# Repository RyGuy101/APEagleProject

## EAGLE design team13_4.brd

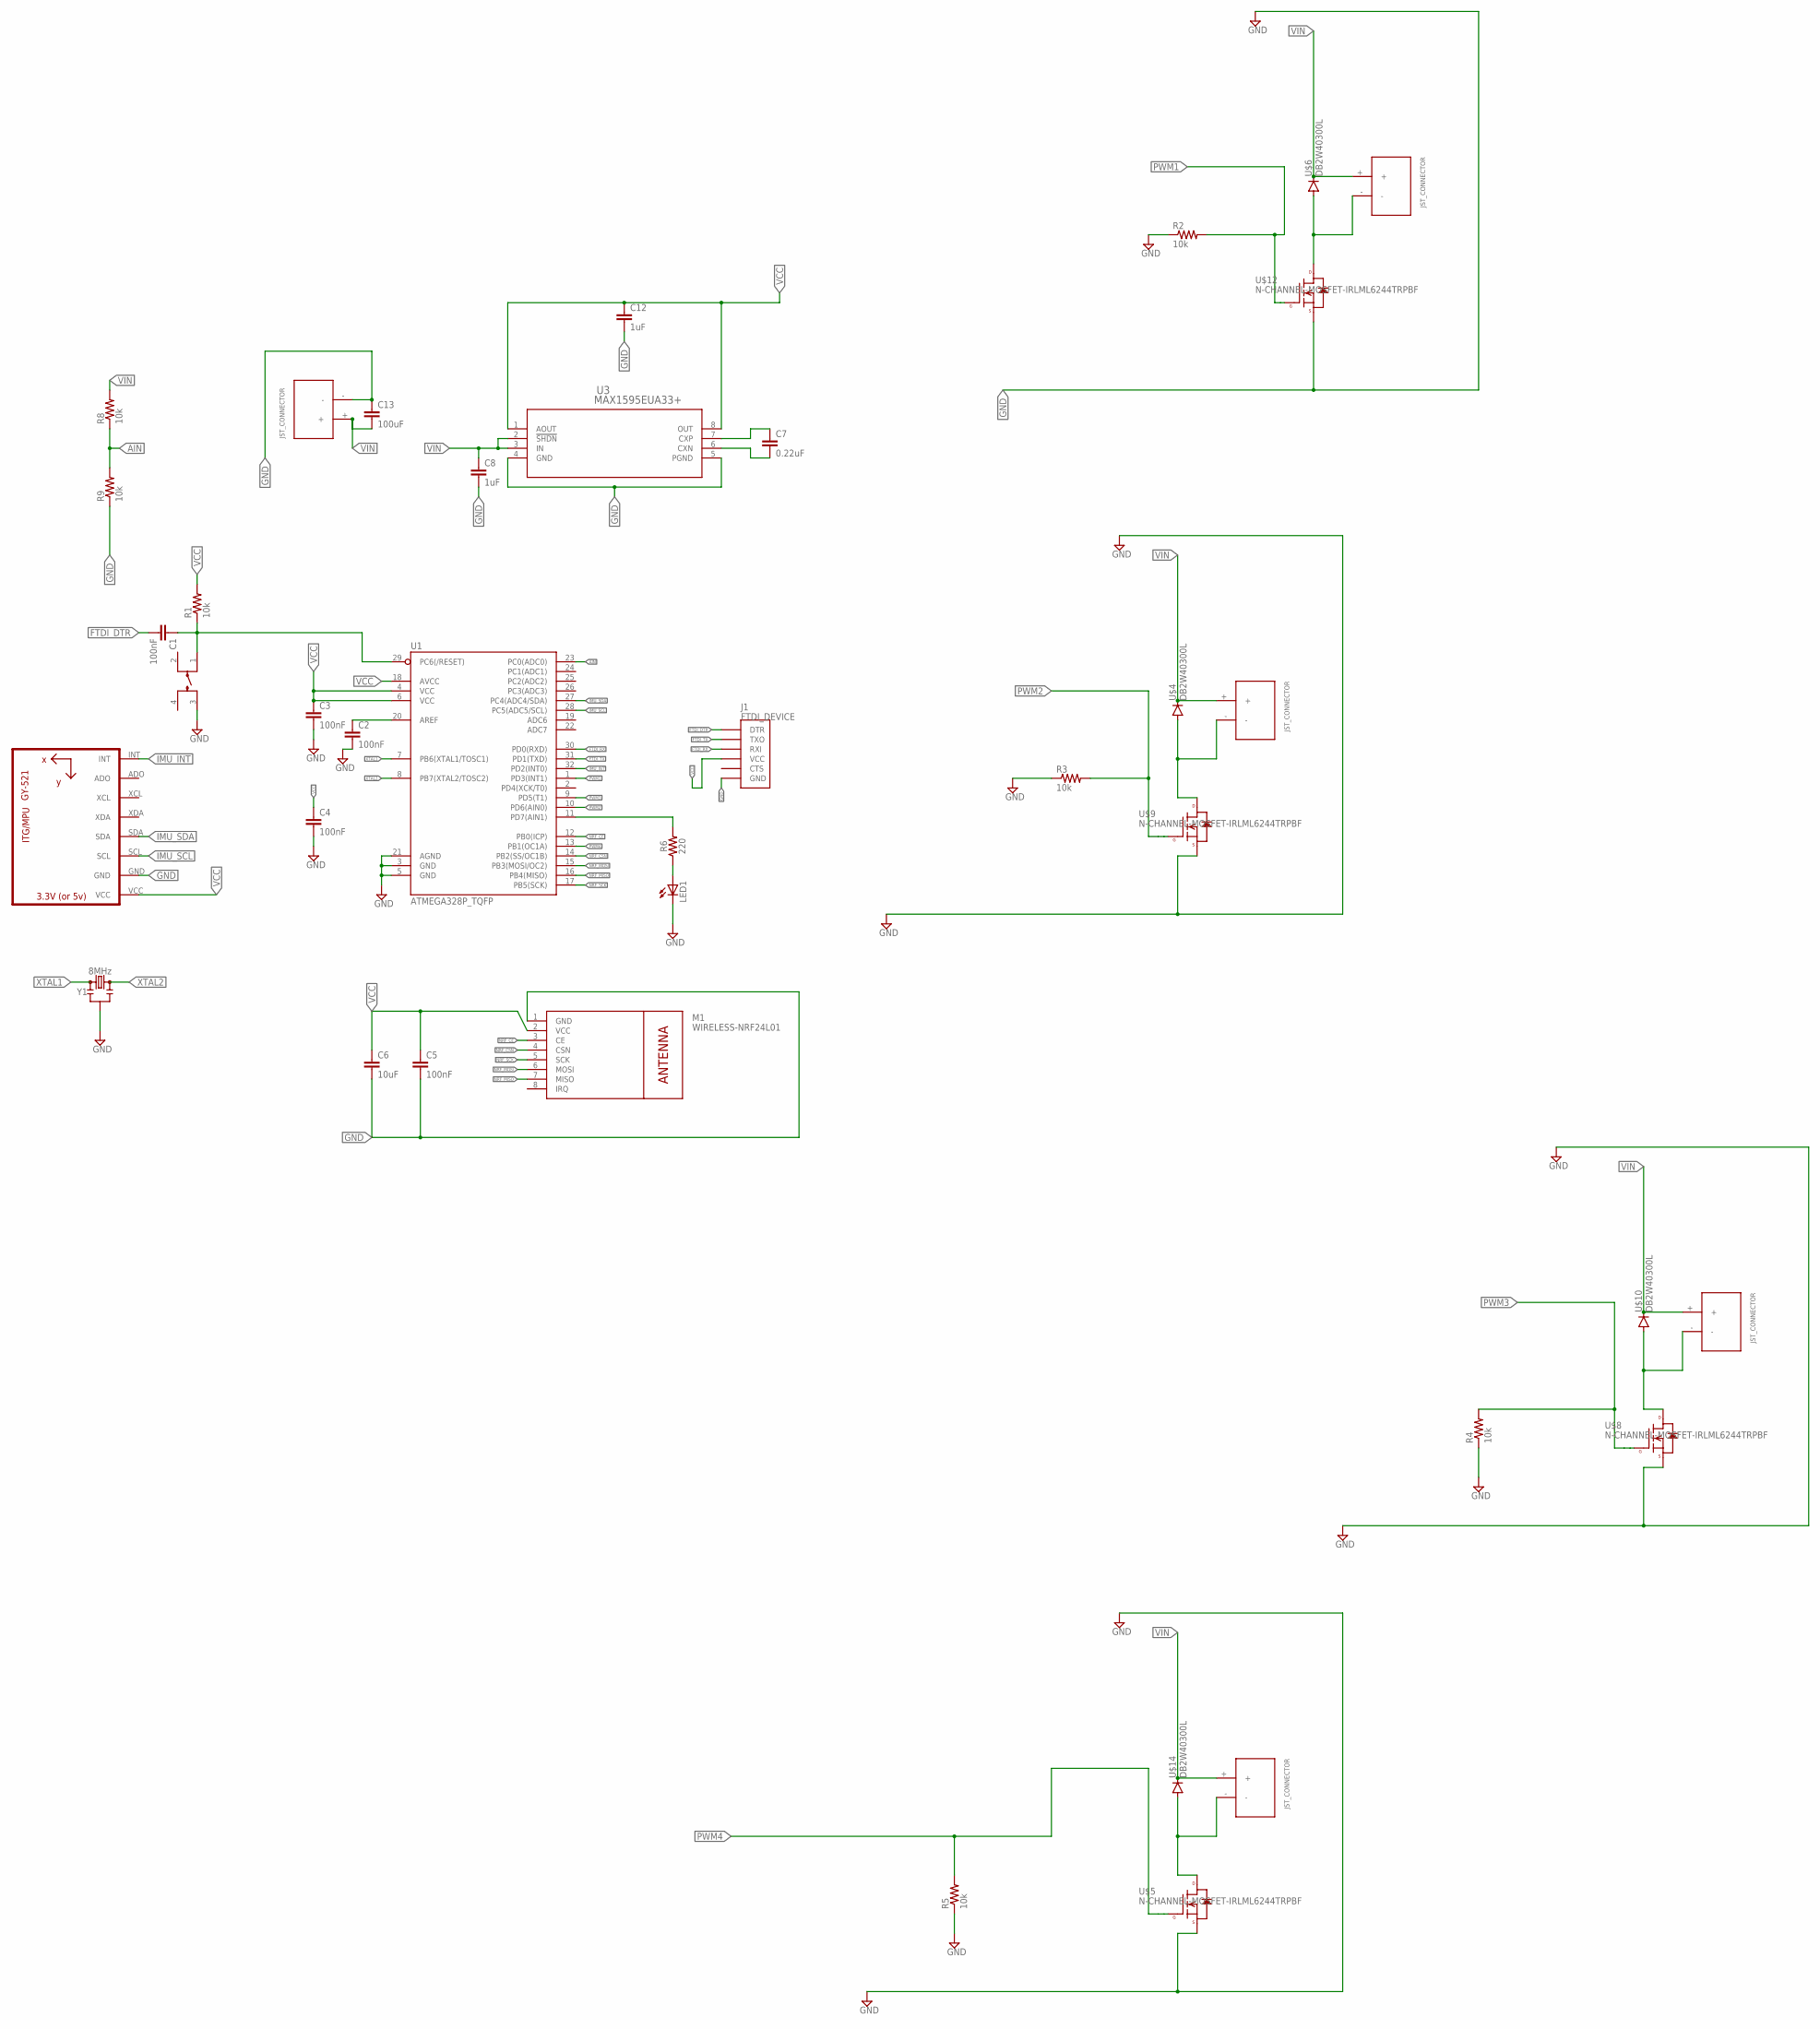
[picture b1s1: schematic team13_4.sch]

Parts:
C1, C2, C3, C4, C5: 100nF; C0603
C6: 10uF; C0603
C7: 0.22uF; C0603
C8, C12: 1uF; C0805
C13: 100uF; C1210
J1: FTDI_DEVICE; FTDI_DEVICE_SIDE
LED1: LED1206; LED-1206
M1: WIRELESS-NRF24L01
R1, R8, R9: 10k; R0603
R2, R3, R4, R5: 10k; 0603-RES
R6: 220; 0603
U1: ATMEGA328P_TQFP; TQFP32-08
U2: GY-521MPU6050; GY-521
U3: MAX1595EUA33+; 21-0036K
U$1: LL3301NF065QG
U$3, U$7, U$11, U$15, U$19: JST_CONNECTOR_FEMALE
U$4, U$6, U$10, U$14: DB2W40300L; MINI2-F3-B
U$5, U$8, U$9, U$12: N-CHANNEL-MOSFET-IRLML6244TRPBF; SOT23-3
Y1: 8MHz; RESONATOR-SMD-3.2X1.3

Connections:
AIN: R8.1, R9.2, U1.23 (PC0(ADC0))
FTDI_DTR: C1.2, J1.P$1 (DTR)
FTDI_RX: J1.P$3 (RXI), U1.30 (PD0(RXD))
FTDI_TX: J1.P$2 (TXO), U1.31 (PD1(TXD))
GND: C2.2, C3.2, C4.2, C5.2, C6.2, C8.2, C12.2, C13.1, J1.P$6 (GND), LED1.C, M1.1 (GND), R2.1, R3.1, R4.1, R5.1, R9.1, U1.3 (GND), U1.5 (GND), U1.21 (AGND), U2.GND, U3.4 (GND), U3.5 (PGND), U$1.3, U$5.2 (S), U$8.2 (S), U$9.2 (S), U$12.2 (S), U$19.-, Y1.2
IMU_INT: U1.32 (PD2(INT0)), U2.INT
IMU_SCL: U1.28 (PC5(ADC5/SCL)), U2.SCL
IMU_SDA: U1.27 (PC4(ADC4/SDA)), U2.SDA
unnamed: C1.1, R1.1, U1.29 (PC6(/RESET)), U$1.1
unnamed: C2.1, U1.20 (AREF)
unnamed: U$3.-, U$4.POS (PPIN), U$9.3 (D)
unnamed: C7.1, U3.7 (CXP)
unnamed: R6.2, U1.11 (PD7(AIN1))
unnamed: U$6.POS (PPIN), U$7.-, U$12.3 (D)
unnamed: C7.2, U3.6 (CXN)
unnamed: LED1.A, R6.1
unnamed: U$8.3 (D), U$10.POS (PPIN), U$11.-
unnamed: U$5.3 (D), U$14.POS (PPIN), U$15.-
NRF_CE: M1.3 (CE), U1.12 (PB0(ICP))
NRF_CSN: M1.4 (CSN), U1.14 (PB2(SS/OC1B))
NRF_MISO: M1.7 (MISO), U1.16 (PB4(MISO))
NRF_MOSI: M1.6 (MOSI), U1.15 (PB3(MOSI/OC2))
NRF_SCK: M1.5 (SCK), U1.17 (PB5(SCK))
PWM1: R2.2, U1.1 (PD3(INT1)), U$12.1 (G)
PWM2: R3.2, U1.10 (PD6(AIN0)), U$9.1 (G)
PWM3: R4.2, U1.9 (PD5(T1)), U$8.1 (G)
PWM4: R5.2, U1.13 (PB1(OC1A)), U$5.1 (G)
VCC: C3.1, C4.1, C5.1, C6.1, C12.1, J1.P$4 (VCC), M1.2 (VCC), R1.2, U1.4 (VCC), U1.6 (VCC), U1.18 (AVCC), U2.VCC, U3.1 (AOUT), U3.8 (OUT)
VIN: C8.1, C13.2, R8.2, U3.2 (!SHDN), U3.3 (IN), U$3.+, U$4.NEG (GPIN), U$6.NEG (GPIN), U$7.+, U$10.NEG (GPIN), U$11.+, U$14.NEG (GPIN), U$15.+, U$19.+
XTAL1: U1.7 (PB6(XTAL1/TOSC1)), Y1.1
XTAL2: U1.8 (PB7(XTAL2/TOSC2)), Y1.3

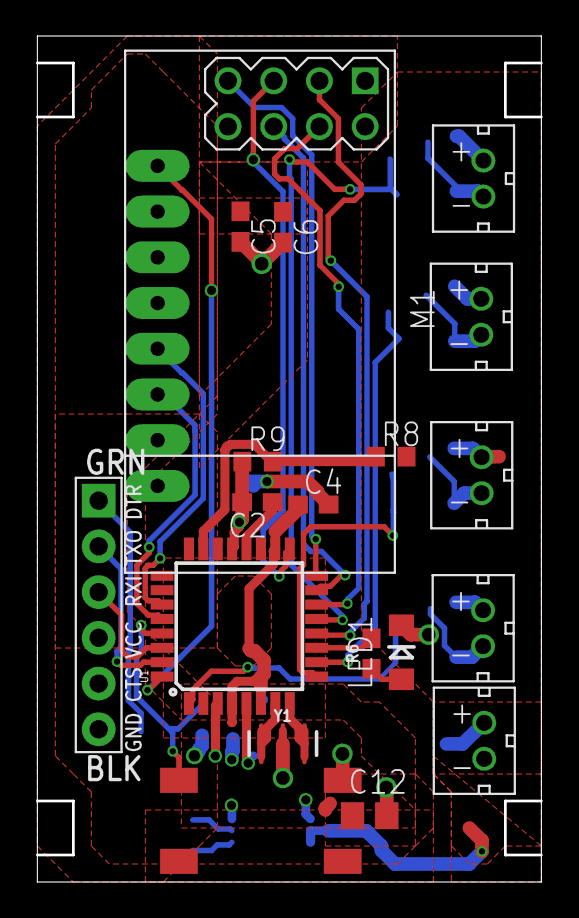
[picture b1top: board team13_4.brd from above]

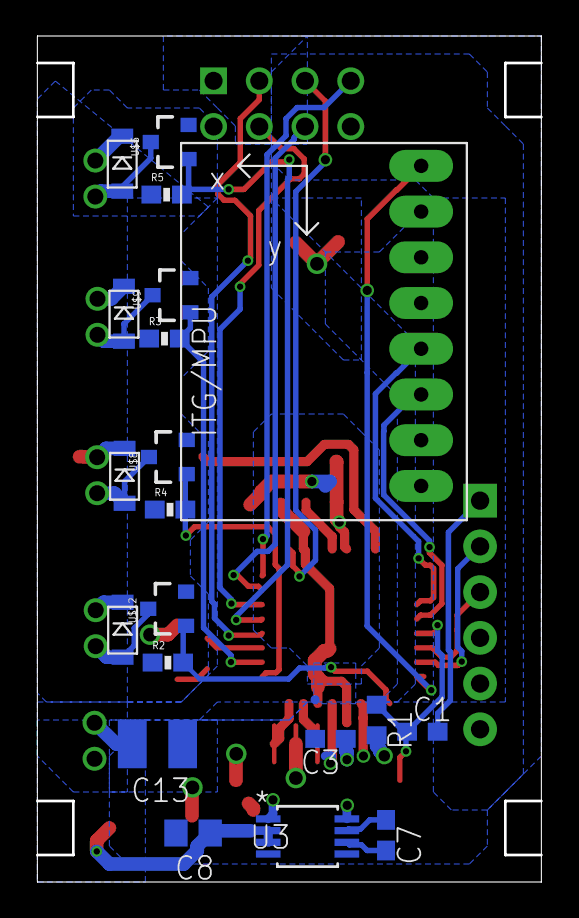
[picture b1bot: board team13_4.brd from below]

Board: 2 copper layers, 28.0 x 46.8 mm, 39 parts (20 on the bottom side), 31 nets.

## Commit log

2018-01-28 Added microcontroller, some decoupling capacitors, headers for FTDI
2018-01-28 Made gitignore
2018-01-29 Added Will's changes
2018-01-29 Added eagle.epf to gitignore
2018-01-29 Added IMU
2018-01-29 Create low side driver
2018-01-29 Updated connections to radio module
2018-01-30 Added buck-boost converter
2018-01-30 Added JST connector
2018-01-30 Added separate radio & buck boost sch
2018-01-30 Added ftdi & decoupling capacitor sch
2018-01-30 added gyro & voltage divider sch
2018-01-30 Added decoupling capacitors to radio module
2018-01-31 Updated schematic. TODO: voltage divider, voltage regulator, motor driver, battery
2018-02-01 Add files via upload
    Lots of stuff
2018-02-01 Updated PWM pins
2018-02-01 Added circuit for crystal oscillator
2018-02-02 Fixed stuff. Replaced crystal & voltage regulator.
2018-02-02 Fixed RX and TX connections
2018-02-02 Made push button library
2018-02-02 Fixed capacitor value
2018-02-02 Fixed some stuff
2018-02-04 Updated capacitors for voltage regulator
2018-02-04 Fixed many overlapping pin ERC errors.
2018-02-04 Saved fixed schematic
2018-02-04 Switched from crystal oscillator to ceramic resonator
2018-02-04 Fixed some of the weird angles
2018-02-04 Removed all angled wires
2018-02-04 Fixed ERC warnings about VCC and GND
2018-02-04 Modified LED Resistor value
2018-02-04 Added changes to voltage regulator and cleaned up pushbutton library.
2018-02-04 "Fixed" another warning caused by voltage regulator.
2018-02-08 Started board design. I love Eagle it's so easy to use.... is a sentence never said by anyone ever.
2018-02-08 Fixed button library. Somehow I had made the pads 2x too big.
2018-02-08 Found the setting for 45 degree routing
2018-02-09 Everything is connected except VCC and GND. But it's really messy and it might even be impossible to connect them successfully without redoing everything.
2018-02-09 Routed FTDI_TX
2018-02-10 Added layout3 (Plane Layout), and routed most of the board. Outstanding issues remain.
2018-02-13 Revision #2 to send
2018-02-13 Checked with oshpark
2018-02-19 Attempted to make improvements. NOTE: crystal is unattached
2018-02-19 Alleviated plane constrictions and stuff.
2018-02-19 fixed components on top of buttons
2018-02-19 Remembered to command+s this time
2018-02-20 Adjusted pushbutton and nearby components
2018-02-20 lkdjhflcsnrhglsefhglwkfghulicurhngihxfhwleurqh;bk
2018-02-20 some bottle neck improvements

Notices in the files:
parts and their libraries:
LilyPad-Wearables: Licensing:Creative Commons ShareAlike 4.0 International - https://creativecommons.org/licenses/by-sa/4.0
